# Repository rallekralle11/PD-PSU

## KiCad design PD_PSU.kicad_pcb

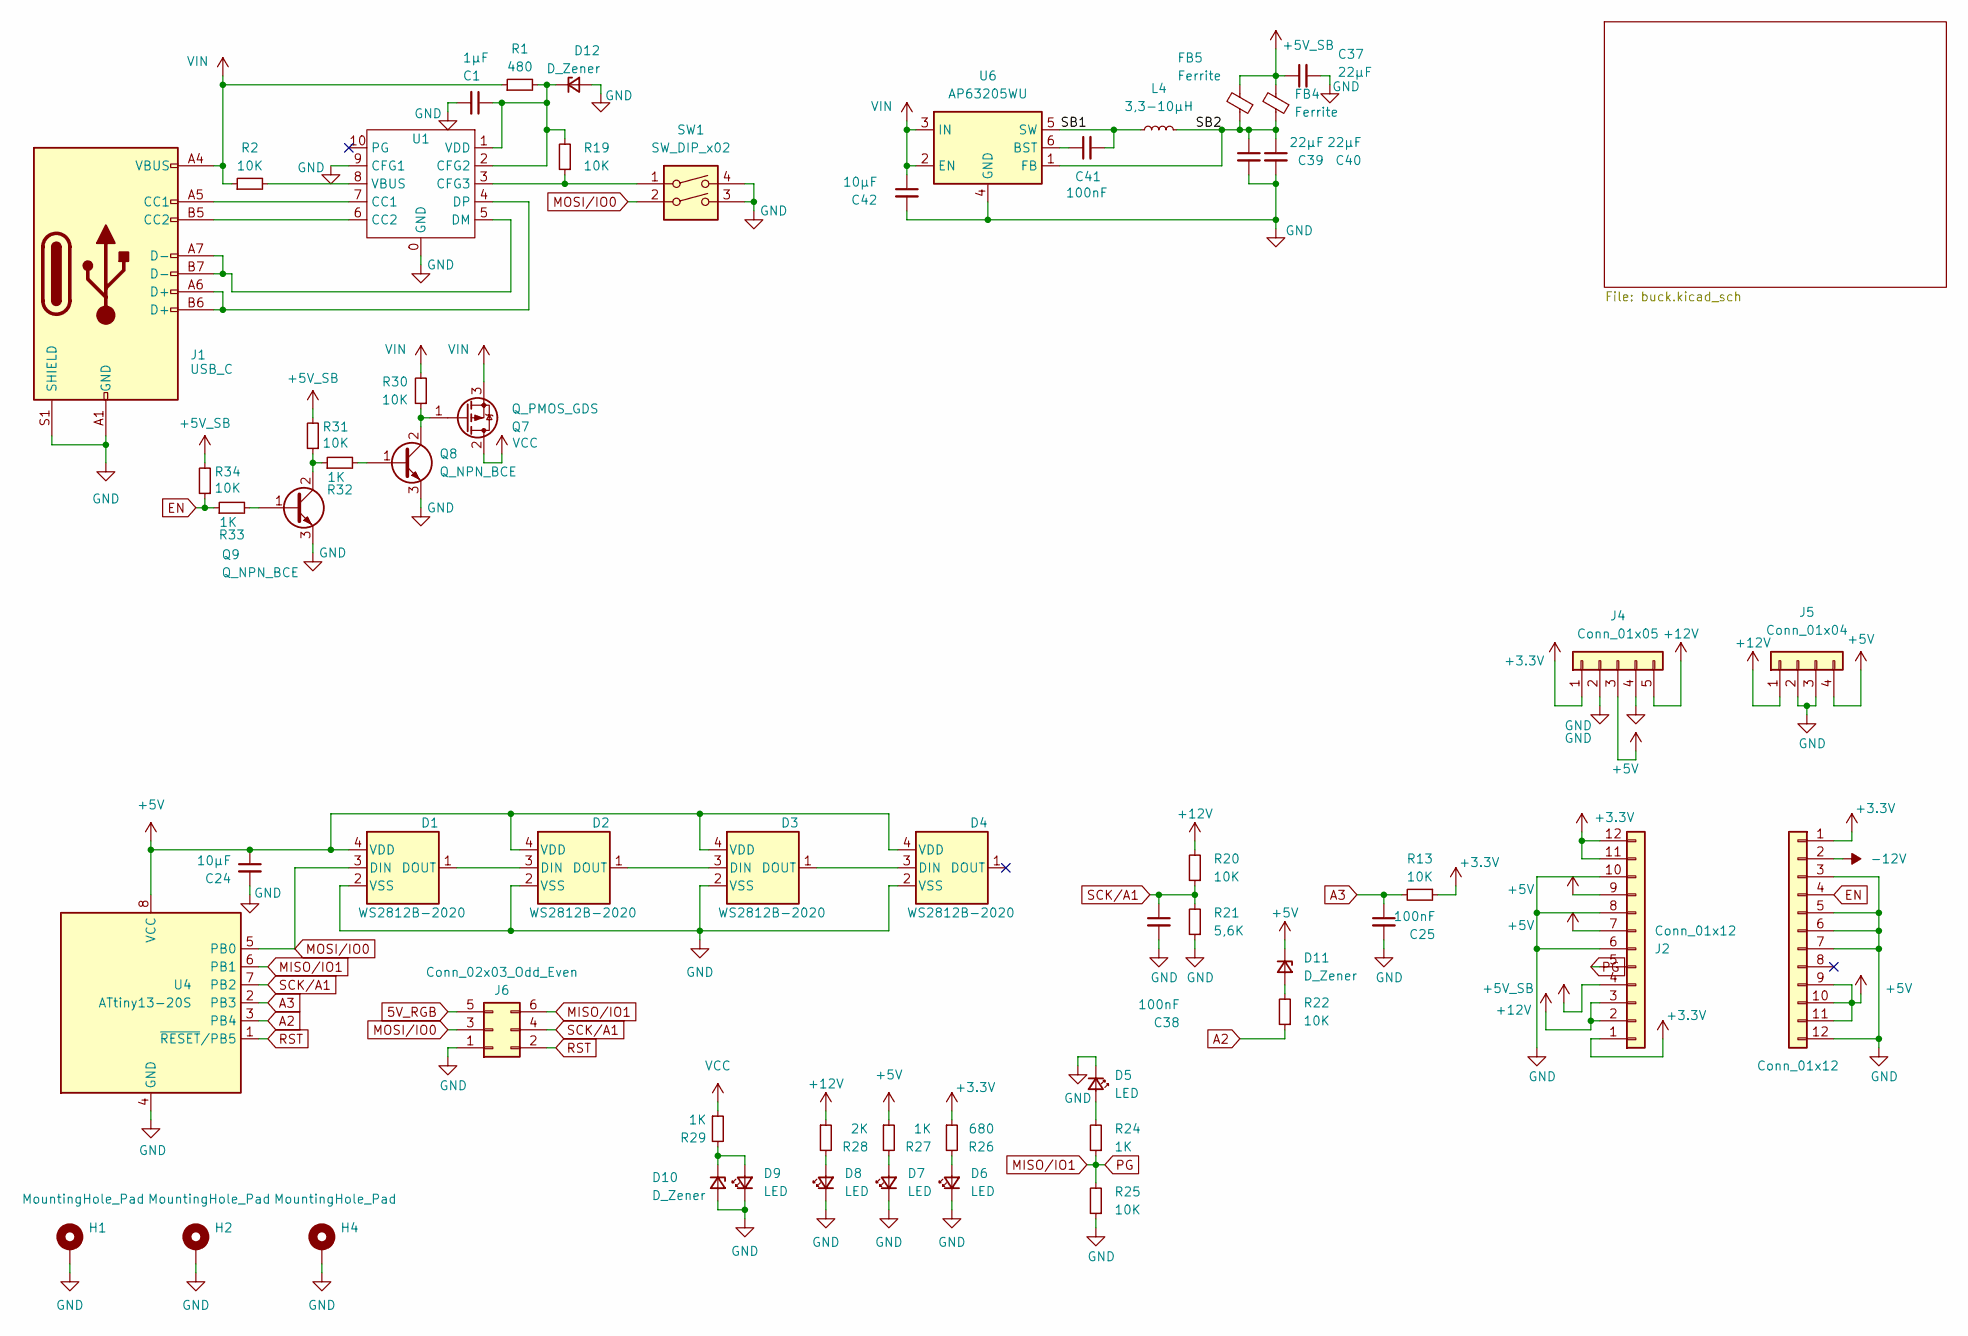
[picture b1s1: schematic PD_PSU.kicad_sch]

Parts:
C1: 1µF; C_0603_1608Metric
C24: 10µF; C_0603_1608Metric
C25, C38, C41: 100nF; C_0402_1005Metric
C37: 22µF; C_0603_1608Metric
C39, C40: 22µF; C_0805_2012Metric
C42: 10µF; C_0805_2012Metric
D1, D2, D3, D4: WS2812B-2020; LED_WS2812B-2020_PLCC4_2.0x2.0mm; LCSC C965555
D5, D6, D7, D8, D9: LED; LED_0402_1005Metric
D10, D11, D12: D_Zener; D_SOD-323
FB4, FB5: Ferrite; R_0402_1005Metric
H1, H2, H4: MountingHole_Pad; MountingHole_3.2mm_M3_Pad
J1: USB_C; USB_C_Receptacle_GCT_USB4105-xx-A_16P_TopMnt_Horizontal
J2, J3: Conn_01x12; TerminalBlock_RND_205-00011_1x12_P5.00mm_Horizontal
J4: Conn_01x05; PinSocket_1x05_P2.54mm_Vertical
J5: Conn_01x04; PinSocket_1x04_P2.54mm_Vertical
J6: Conn_02x03_Odd_Even; PinHeader_2x03_P2.54mm_Vertical
L4: 3,3-10µH; L_Cenker_CKCS4020
Q7: Q_PMOS_GDS; SOT-23-3
Q8, Q9: Q_NPN_BCE; SOT-23-3
R1: 480; R_0402_1005Metric
R2, R13, R19, R20, R22, R25, R30, R31, R34: 10K; R_0402_1005Metric
R21: 5,6K; R_0402_1005Metric
R24, R27, R29, R32, R33: 1K; R_0402_1005Metric
R26: 680; R_0402_1005Metric
R28: 2K; R_0402_1005Metric
SW1: SW_DIP_x02; SW_DIP_SPSTx02_Slide_6.7x6.64mm_W7.62mm_P2.54mm_LowProfile
U1: SOIC-10_3.9x4.9mm_P1mm
U4: ATtiny13-20S; SOIC-8W_5.3x5.3mm_P1.27mm
U6: AP63205WU; TSOT-23-6

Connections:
5V_RGB: J6.5
+3.3V: J2.1, J2.11, J2.12, J3.1, J4.1, R13.1, R26.1; also elsewhere on the board
+5V_SB: C37.1, FB4.2, FB5.2, J2.4, R31.2, R34.2
+12V: J2.2, J2.3, J4.5, J5.1, R20.2, R28.1; also elsewhere on the board
-12V: J3.2; also elsewhere on the board
/SB1: C41.2, L4.1, U6.5 (SW)
/SB2: C39.1, C40.1, FB4.1, FB5.1, L4.2, U6.1 (FB)
A2: R22.1, U4.3 (PB4); also elsewhere on the board
A3: C25.1, R13.2, U4.2 (PB3)
EN: J3.4, R33.1, R34.1
GND: C1.2, C24.2, C25.2, C37.2, C38.2, C39.2, C40.2, C42.2, D1.2 (VSS), D2.2 (VSS), D3.2 (VSS), D4.2 (VSS), D5.1 (K), D6.1 (K), D7.1 (K), D8.1 (K), D9.1 (K), D10.2 (A), D12.2 (A), H1.1, H2.1, H4.1, J1.A1 (GND), J1.A12 (GND), J1.B1 (GND), J1.B12 (GND), J1.S1 (SHIELD), J2.6, J2.8, J2.10, J3.3, J3.5, J3.6, J3.7, J3.12, J4.2, J4.4, J5.2, J5.3, J6.1, Q8.3 (E), Q9.3 (E), R21.1, R25.1, SW1.3, SW1.4, U1.0 (GND), U1.9 (CFG1), U4.4 (GND), U6.4 (GND); also elsewhere on the board
MOSI/IO0: D1.3 (DIN), J6.3, SW1.2, U4.5 (PB0)
unnamed: D1.1 (DOUT), D2.3 (DIN)
unnamed: D2.1 (DOUT), D3.3 (DIN)
unnamed: D3.1 (DOUT), D4.3 (DIN)
unnamed: D6.2 (A), R26.2
unnamed: D7.2 (A), R27.2
unnamed: D8.2 (A), R28.2
unnamed: D9.2 (A), D10.1 (K), R29.2
unnamed: D11.2 (A), R22.2
unnamed: C1.1, D12.1 (K), R1.2, R19.2, U1.1 (VDD), U1.2 (CFG2)
unnamed: J1.A5 (CC1), U1.7 (CC1)
unnamed: J1.B5 (CC2), U1.6 (CC2)
unnamed: Q7.1 (G), Q8.2 (C), R30.1
unnamed: Q8.1 (B), R32.2
unnamed: Q9.1 (B), R33.2
unnamed: Q9.2 (C), R31.1, R32.1
unnamed: R19.1, SW1.1, U1.3 (CFG3)
unnamed: J1.A7 (D-), J1.B7 (D-), U1.5 (DM)
unnamed: J1.A6 (D+), J1.B6 (D+), U1.4 (DP)
unnamed: R2.2, U1.8 (VBUS)
unnamed: C41.1, U6.6 (BST)
RST: J6.2, U4.1 (~RESET/PB5)
SCK/A1: C38.1, J6.4, R20.1, R21.2, U4.7 (PB2)
VCC: Q7.2 (D), R29.1; also elsewhere on the board
VIN: C42.1, J1.A4 (VBUS), J1.A9 (VBUS), J1.B4 (VBUS), J1.B9 (VBUS), Q7.3 (S), R1.1, R2.1, R30.2, U6.2 (EN), U6.3 (IN)

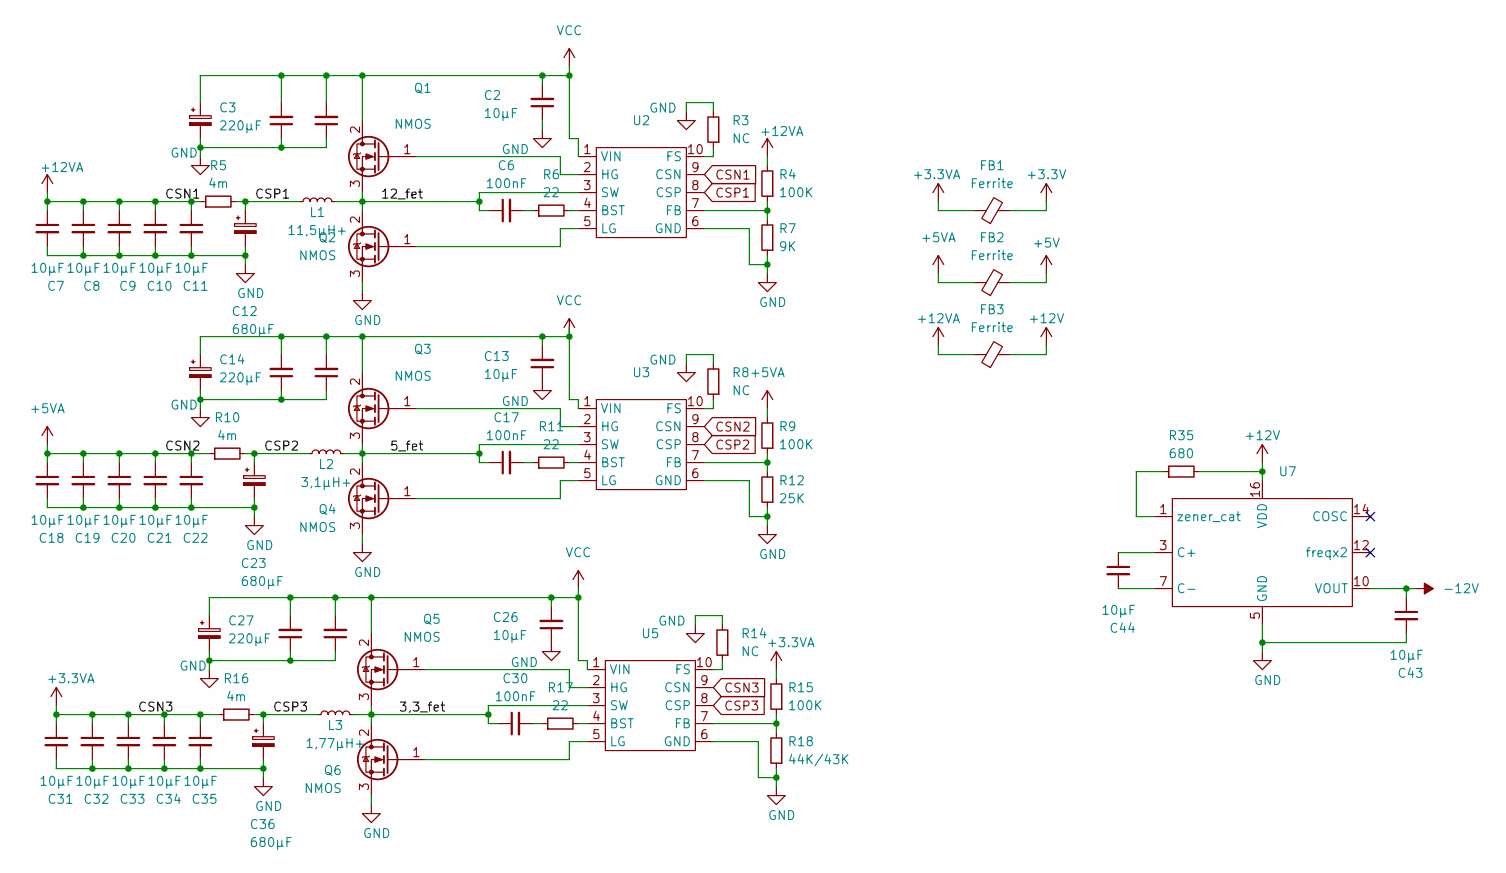
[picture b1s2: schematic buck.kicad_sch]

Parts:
C2, C7, C8, C9, C10, C11, C13, C18, C19, C20, C21, C22, C26, C31, C32, C33, C34, C35, C43, C44: 10µF; C_0805_2012Metric
C3, C14, C27: 220µF; CP_Elec_10x10
C4, C5, C15, C16, C28, C29: 4,7µF; C_0805_2012Metric
C6, C17, C30: 100nF; C_0402_1005Metric
C12, C23, C36: 680µF; CP_Elec_10x10
FB1, FB2, FB3: Ferrite; BPH853025R5-101T
L1: 11,5µH+; L_TaiTech_TMPC1265_13.5x12.5mm
L2: 3,1µH+; L_TaiTech_TMPC1265_13.5x12.5mm
L3: 1,77µH+; L_TaiTech_TMPC1265_13.5x12.5mm
Q1, Q2, Q3, Q4, Q5, Q6: NMOS; TO-252-2
R3, R8, R14: NC; R_0402_1005Metric
R4, R9, R15: 100K; R_0402_1005Metric
R5, R10, R16: 4m; R_2512_6332Metric
R6, R11, R17: 22; R_0402_1005Metric
R7: 9K; R_0402_1005Metric
R12: 25K; R_0402_1005Metric
R18: 44K/43K; R_0402_1005Metric
R35: 680; R_0402_1005Metric
U2, U3, U5: SOIC-10_3.9x4.9mm_P1mm
U7: SOIC-16W_7.5x10.3mm_P1.27mm

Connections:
+3.3V: FB1.2; also elsewhere on the board
+12V: FB3.2, R35.2, U7.16 (VDD); also elsewhere on the board
-12V: C43.1, U7.10 (VOUT); also elsewhere on the board
/buck/3,3_fet: C30.1, L3.2, Q5.3 (S), Q6.2 (D), U5.3 (SW)
/buck/5_fet: C17.1, L2.2, Q3.3 (S), Q4.2 (D), U3.3 (SW)
/buck/12_fet: C6.1, L1.2, Q1.3 (S), Q2.2 (D), U2.3 (SW)
CSN1: C7.1, C8.1, C9.1, C10.1, C11.1, FB3.1, R4.2, R5.1, U2.9 (CSN)
CSN2: C18.1, C19.1, C20.1, C21.1, C22.1, FB2.1, R9.2, R10.1, U3.9 (CSN)
CSN3: C31.1, C32.1, C33.1, C34.1, C35.1, FB1.1, R15.2, R16.1, U5.9 (CSN)
CSP1: C12.1, L1.1, R5.2, U2.8 (CSP)
CSP2: C23.1, L2.1, R10.2, U3.8 (CSP)
CSP3: C36.1, L3.1, R16.2, U5.8 (CSP)
GND: C2.1, C3.2, C4.1, C5.1, C7.2, C8.2, C9.2, C10.2, C11.2, C12.2, C13.1, C14.2, C15.1, C16.1, C18.2, C19.2, C20.2, C21.2, C22.2, C23.2, C26.1, C27.2, C28.1, C29.1, C31.2, C32.2, C33.2, C34.2, C35.2, C36.2, C43.2, Q2.3 (S), Q4.3 (S), Q6.3 (S), R3.2, R7.1, R8.2, R12.1, R14.2, R18.1, U2.6 (GND), U3.6 (GND), U5.6 (GND), U7.5 (GND); also elsewhere on the board
unnamed: C6.2, R6.1
unnamed: C17.2, R11.1
unnamed: C30.2, R17.1
unnamed: Q1.1 (G), U2.2 (HG)
unnamed: Q2.1 (G), U2.5 (LG)
unnamed: Q3.1 (G), U3.2 (HG)
unnamed: Q4.1 (G), U3.5 (LG)
unnamed: Q5.1 (G), U5.2 (HG)
unnamed: Q6.1 (G), U5.5 (LG)
unnamed: R6.2, U2.4 (BST)
unnamed: R4.1, R7.2, U2.7 (FB)
unnamed: R3.1, U2.10 (FS)
unnamed: R11.2, U3.4 (BST)
unnamed: R9.1, R12.2, U3.7 (FB)
unnamed: R8.1, U3.10 (FS)
unnamed: R17.2, U5.4 (BST)
unnamed: R15.1, R18.2, U5.7 (FB)
unnamed: R14.1, U5.10 (FS)
unnamed: C44.1, U7.3 (C+)
unnamed: C44.2, U7.7 (C-)
unnamed: R35.1, U7.1 (zener_cat)
VCC: C2.2, C3.1, C4.2, C5.2, C13.2, C14.1, C15.2, C16.2, C26.2, C27.1, C28.2, C29.2, Q1.2 (D), Q3.2 (D), Q5.2 (D), U2.1 (VIN), U3.1 (VIN), U5.1 (VIN); also elsewhere on the board

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
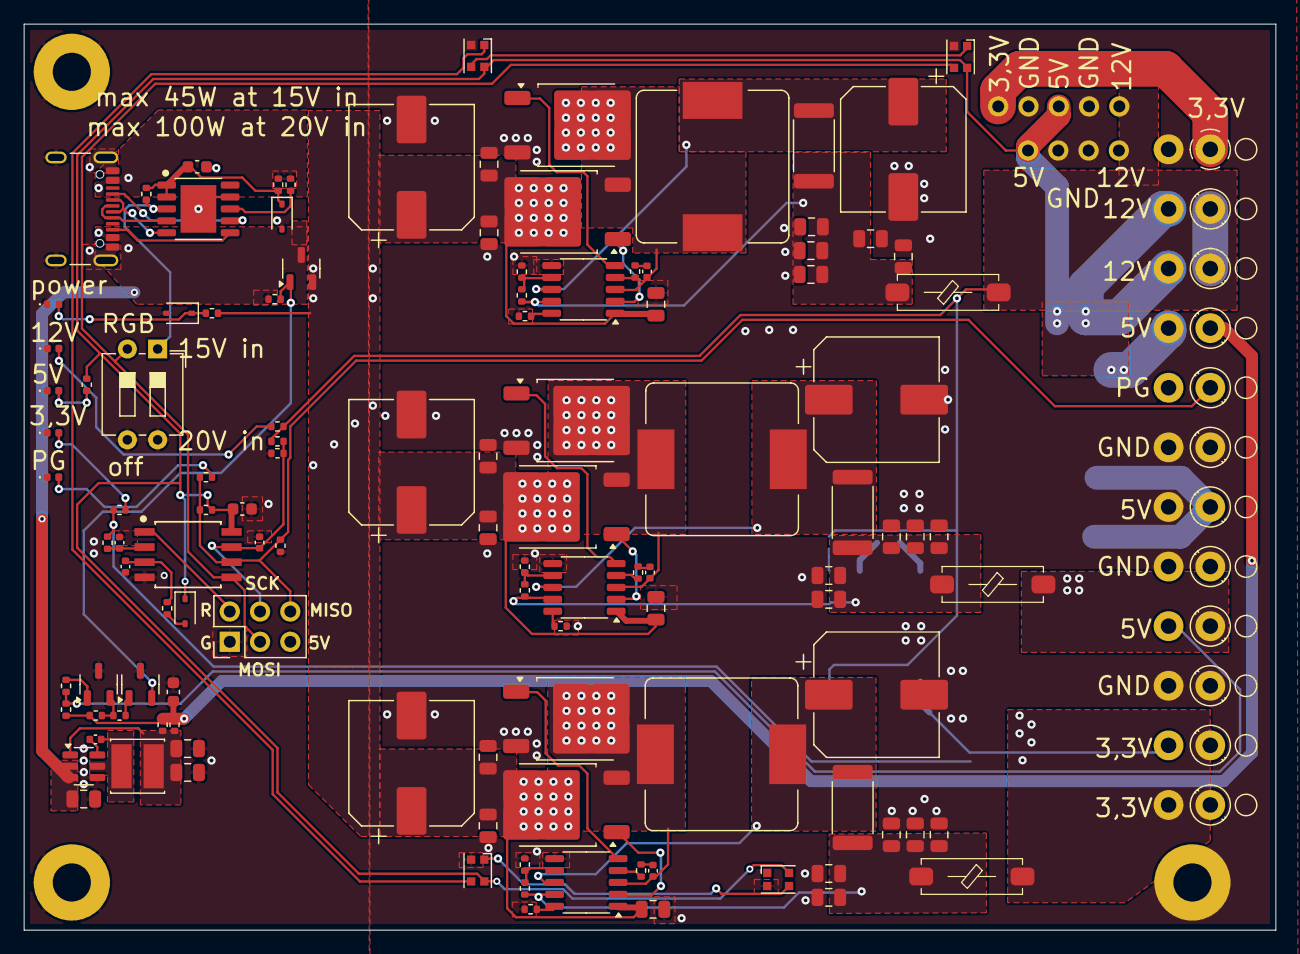
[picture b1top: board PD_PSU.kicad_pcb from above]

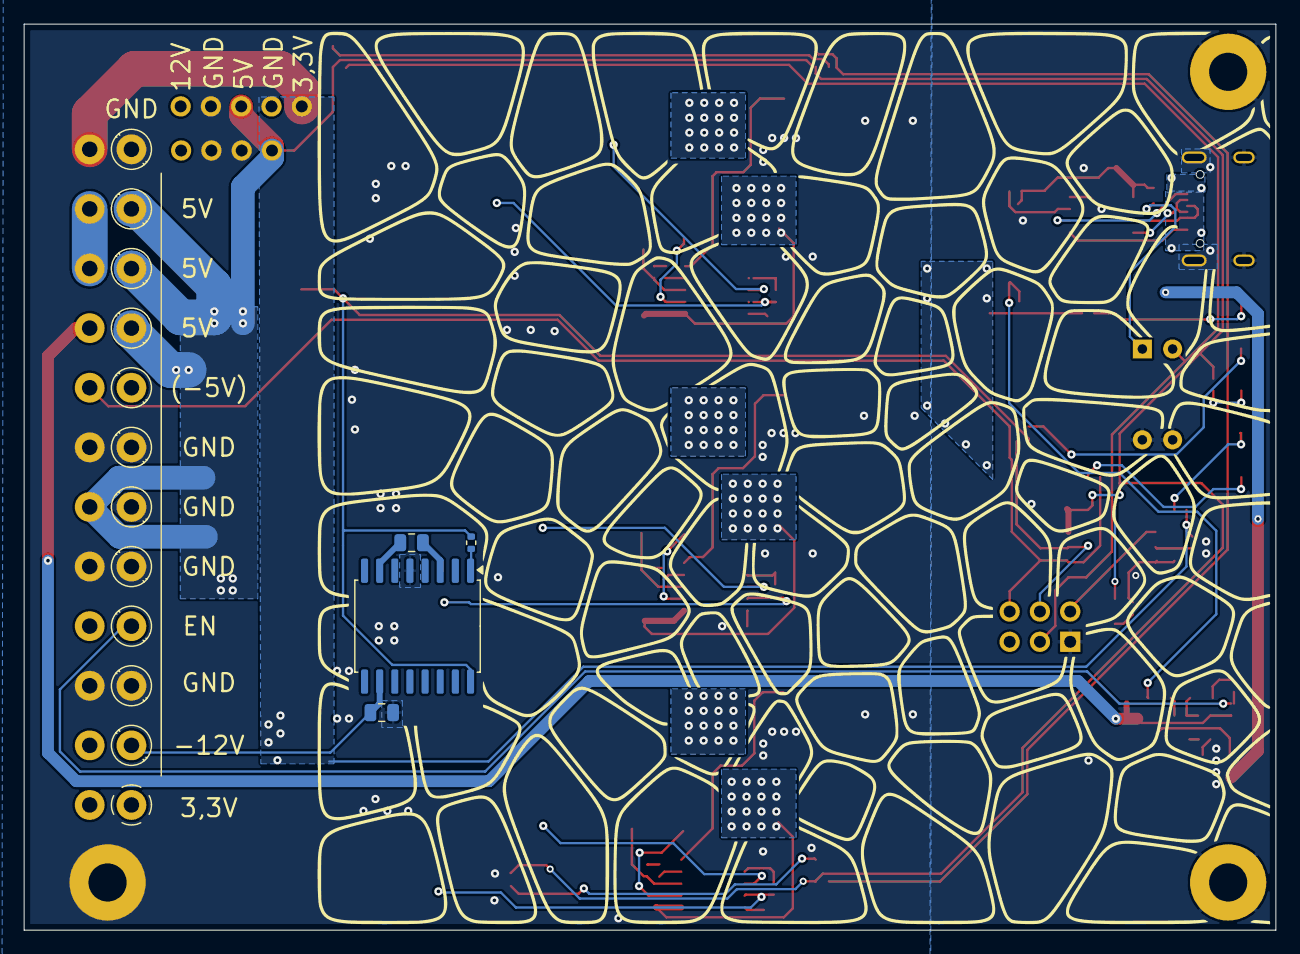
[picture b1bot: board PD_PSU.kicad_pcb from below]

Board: 2 copper layers, 105.0 x 76.0 mm, 127 parts (5 on the bottom side), 68 nets.

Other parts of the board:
C37#2: 100nF; C_0402_1005Metric
R24#2: 1K; R_0402_1005Metric

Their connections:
A2: C37#2.1; also elsewhere on the board
GND: C37#2.2; also elsewhere on the board

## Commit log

2024-10-17 init
